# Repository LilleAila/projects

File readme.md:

# Small programming projects

Some small projects organized by year and month with development environments managed by nix and direnv

## Devshell templates
Usage:
```bash
# .envrc
use flake github:LilleAila/projects#nix
use flake github:LilleAila/projects#python
use nix
```
```nix
# shell.nix
{ pkgs ? import <nixpkgs> {} }: with pkgs; mkShell {
  nativeBuildInputs = [
    (python311.withPackages (ps: with ps; [
      matplotlib
      numpy
      tkinter
    ]))
  ];
}
```

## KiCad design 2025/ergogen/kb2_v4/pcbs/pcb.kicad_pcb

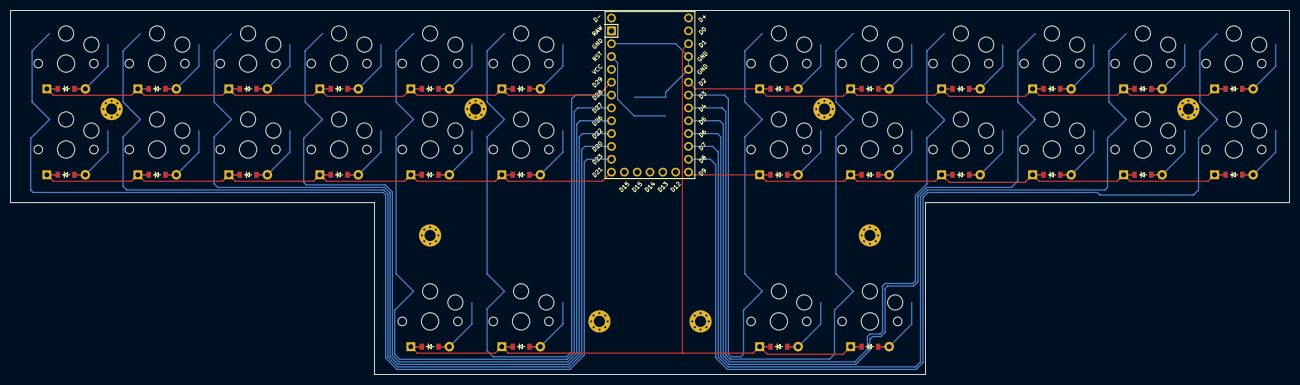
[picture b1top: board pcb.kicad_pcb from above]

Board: 2 copper layers, 253.0 x 72.0 mm, 66 parts (0 on the bottom side), 47 nets.

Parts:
B1: SW_TACT_ALPS_SKQGABE010
D1, D2, D3, D4, D5, D6, D7, D8, D9, D10, D11, D12, D13, D14, D15, D16, D17, D18, D19, D20, D21, D22, D23, D24, D25, D26, D27, D28: ComboDiode
MCU1: ProMicro
S1, S2, S3, S4, S5, S6, S7, S8, S9, S10, S11, S12, S13, S14, S15, S16, S17, S18, S19, S20, S21, S22, S23, S24, S25, S26, S27, S28: PG1350
_1, _2, _3, _4, _5, _6, _7, _8: Mount_Hole_2.2mm_Pad_Via

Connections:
D1: D25.1, D26.1, D27.1, D28.1, MCU1.20
D2: D14.1, D16.1, D18.1, D20.1, D22.1, D24.1, MCU1.23
D3: MCU1.24, S13.1, S14.1, S27.1
D4: MCU1.25, S15.1, S16.1, S28.1
D5: MCU1.26, S17.1, S18.1
D6: MCU1.27, S19.1, S20.1
D7: MCU1.28, S21.1, S22.1
D8: MCU1.29, S23.1, S24.1
D9: D13.1, D15.1, D17.1, D19.1, D21.1, D23.1, MCU1.30
D20: MCU1.10, S3.1, S4.1
D21: D1.1, D3.1, D5.1, D7.1, D9.1, D11.1, MCU1.12
D22: MCU1.9, S5.1, S6.1
D23: MCU1.11, S1.1, S2.1
D26: MCU1.8, S7.1, S8.1
D27: MCU1.7, S9.1, S10.1, S25.1
D28: MCU1.6, S11.1, S12.1, S26.1
D29: D2.1, D4.1, D6.1, D8.1, D10.1, D12.1, MCU1.5
GND: B1.1, MCU1.2, MCU1.21, MCU1.22
RST: B1.2, MCU1.3
index_lbottom: D9.2, S9.2
index_ltop: D10.2, S10.2
index_rbottom: D15.2, S15.2
index_rtop: D16.2, S16.2
inner_lbottom: D11.2, S11.2
inner_ltop: D12.2, S12.2
inner_lttop: D26.2, S26.2
inner_rbottom: D13.2, S13.2
inner_rtop: D14.2, S14.2
inner_rttop: D27.2, S27.2
middle_lbottom: D7.2, S7.2
middle_ltop: D8.2, S8.2
middle_rbottom: D17.2, S17.2
middle_rtop: D18.2, S18.2
outer_lbottom: D1.2, S1.2
outer_ltop: D2.2, S2.2
outer_lttop: D25.2, S25.2
outer_rbottom: D23.2, S23.2
outer_rtop: D24.2, S24.2
outer_rttop: D28.2, S28.2
pinky_lbottom: D3.2, S3.2
pinky_ltop: D4.2, S4.2
pinky_rbottom: D21.2, S21.2
pinky_rtop: D22.2, S22.2
ring_lbottom: D5.2, S5.2
ring_ltop: D6.2, S6.2
ring_rbottom: D19.2, S19.2
ring_rtop: D20.2, S20.2

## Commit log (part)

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2024-07-08 Initial commit
    Added devshells and stuff
2024-07-08 added python
2024-07-08 added js
2024-07-08 added missing stuff to js shell
2024-07-08 added astro shel
2024-07-08 added texlive
2024-07-08 fixed pyright in python shell
2024-07-08 added stuff to readme
2024-07-08 added lua
2024-07-08 added rust
2024-07-08 added rust anal
2024-07-10 ting og sånt
2024-08-19 did some stuff
2024-08-21 jupyter: init
2024-08-22 el eller annen oppgave
2024-08-26 kapittel 1a
2024-08-26 TYPES
2024-08-26 updated til python 3.12
2024-08-29 stein saks papir
2024-08-29 bedre kode og masse kommentarer
2024-08-29 stop unnecessary __init__ when stopping
2024-08-29 mulige forbedringer
2024-08-29 reversed the choices list to be correct when inputting
2024-09-04 tried adding manim
2024-09-05 manim stuff
2024-09-05 readme
2024-09-05 bruker-innlogging med hashing og sånt
2024-09-05 mer ting
2024-09-07 bedre struktur på 03
2024-09-07 skrive oppgaven i 03
2024-09-07 ignore __pycache__
2024-09-07 ignore db in 03
2024-09-07 path arg for db
2024-09-12 masse greie
2024-09-12 quicksort
2024-09-12 tested different activity diagrams
2024-09-13 fikse duplikat
2024-09-14 web scraping stuff
2024-09-15 tried doing unibok dl
2024-09-15 better uml diagram
2024-09-15 unibok ting
2024-09-15 mer unibok ting
2024-09-15 unibok: download file
2024-09-15 get chromium path automatically
2024-09-15 class and better code for unibok thing
2024-09-15 ability to download multiple books
2024-09-15 download entire library
2024-09-16 grenseverdier
2024-09-16 dicts
2024-09-17 ; instead of ,
2024-09-19 fucnitojasner
2024-09-20 project euler problems
2024-09-20 fix type in problem 6
2024-09-20 project euler problem 8
2024-09-20 project euler problem 10
2024-09-20 organize stuff
2024-09-20 project euler readme
2024-09-20 problem 12
2024-09-20 problem 14
2024-09-21 problem 13
2024-09-21 problem 15
2024-09-21 problem 16
2024-09-23 prøve 20240923
2024-09-25 problem 11
2024-09-25 problem 20
2024-09-26 oppdatert koden litt
2024-09-27 unibok: fix path names with /
2024-10-05 proecteuler: renamed files
2024-10-05 p017
2024-10-06 akademika author to calibre format
2024-10-24 diagram for spill
2024-10-24 finish diagram for game
2024-10-28 enemy interface in 10-
2024-10-29 ting
2024-10-31 sudoku ting
2024-10-31 more sudoku
2024-11-01 more progress on sudoku solver
    missing validation function
2024-11-04 finished solver but extremely inefficient
2024-11-05 significantly improve speed
2024-11-06 completely choose pos automatically rather than increment by one in parent
2024-11-06 started doing random stuff in board generation
2024-11-11 pygame: init
2024-11-11 pygame better organization
2024-11-11 oida lol
2024-11-14 more ponging
2024-11-14 paddle collision
2024-11-14 show score
2024-11-14 better score class
2024-11-14 point x value
2024-11-15 animations
2024-11-15 runtime didn't work on graph :(
2024-11-15 more manim stuff
2024-11-16 kontinuitet
2024-11-16 mobject for point on graph
2024-11-16 mer kontinuitet
2024-11-17 organized stuff better
2024-11-17 move both animations into one file
2024-11-18 secant approaching each side
2024-11-18 --amend
2024-11-18 tweak stuff
2024-11-18 derivative to a
2024-11-18 mer derivasjon
2024-11-21 some collision stuff
2024-11-21 fix ball clipping
2024-11-25 Add 1 git-crypt collaborator
    New collaborators:
    2B9B9799 Olai Solsvik <olai.solsvik@gmail.com>
2024-11-25 manim: play audio, git-crypt: init and encrypt manim audio
2024-11-25 start doing bibliotek
2024-11-25 start tui
2024-11-25 more book stuff
2024-11-25 puml diagram
2024-11-25 small tweaks in manim
2024-11-26 heldagsprøve 2024-11-26
2024-11-26 mer heldagsprøve ting
2024-11-27 started adding audio in manim
2024-11-27 remove ceil left from debugging
2024-11-28 manim: add sounds
2024-12-01 julekalendere: init
2024-12-01 knowit: luke 1
2024-12-01 adventofcode: day 1
2024-12-02 knowit: luke 2
2024-12-02 aoc: day 2
2024-12-02 knowit: remove compile stuff
2024-12-03 knowit: start luke 2
2024-12-03 more luke 3
2024-12-03 more knowit 3 aaa
2024-12-03 aoc: day 3
2024-12-03 day 3 aoc explain dotall
2024-12-03 aaaaa
2024-12-04 knowit luke 4
2024-12-05 aoc 4 pt1
2024-12-06 knowit luke 6 start
2024-12-07 luke 6 (ikke ferdig :()
2024-12-07 knowit: luke 7
2024-12-07 knowit: challenges note in readme
2024-12-07 remove unused import
2024-12-08 tried fixing day 6 knowit
2024-12-08 knowit: luke 8
2024-12-08 luke 8 knowit: small time improvement
2024-12-08 gitignore haskell build artefacts
2024-12-08 luke 4 readme and notes
2024-12-09 continued with 6
2024-12-09 remove compiled
2024-12-09 knowit: luke 9
2024-12-09 luke 3 knowit: tried python 😭
2024-12-09 luke 9: tweak syntax
2024-12-10 luke 1: fix small error
2024-12-11 tried doing luke 10
2024-12-11 fixed stupid error i don't even know where came from
2024-12-11 started solving luke 11
2024-12-11 cpp stuff
2024-12-11 finish day 6
2024-12-12 started solving 12
2024-12-12 tried doing more luke 11 :(
2024-12-12 a* search
2024-12-12 get the distance
2024-12-12 more stuff
2024-12-12 tried python on 12
2024-12-12 init potensiell prøve
2024-12-14 tried doing 14
2024-12-15 map ting
2024-12-15 14 readme
2024-12-15 tried starting 15
2024-12-15 tried more on 13
2024-12-24 luke 24
2025-01-06 knowit: add challenges
2025-01-13 nio runde 2
2025-01-16 it2: 14-datasett
2025-01-20 start openstreetmap thing
2025-01-20 simplify api call
2025-01-20 cut off outside bounding box
2025-01-20 get coords from user input
2025-01-21 generate simple 3d model
2025-01-21 clean up
2025-01-21 get epsg automatically
2025-01-21 base plate and walls
2025-01-21 simplify plotting
2025-01-21 area selection and notes
2025-01-21 fix dependencies
2025-01-21 increate base plate height
2025-01-23 it2 oppgaver
2025-01-27 start trying to add jupyter lab
2025-01-27 oppgaver it2
2025-01-30 plotting lol
2025-02-01 started looking at monkeytype stats
2025-02-03 matplotlib
2025-02-06 tried more jupyterlab
2025-02-06 pandas greier
2025-02-06 fikse tall i navn
2025-02-06 add monkeytype and cstimer stuff
2025-02-06 add studietid datasets
2025-02-06 cstimer plotting lol
2025-02-06 studietid
2025-02-06 started monkeytyping
2025-02-06 mer studietid og monkeytype
2025-02-08 add anki and koreader datasets
2025-02-08 book stats
2025-02-08 more koreader
2025-02-09 more koreader 2
2025-02-09 make lsp not error when not error
2025-02-09 anki stats
2025-02-09 anki stat labels
2025-02-09 anki review efficiency
2025-02-09 small diagram tweaks
2025-02-09 more book statistics
2025-02-09 tried more to get jupyterlab to work :(
2025-02-09 jupyterlab: yay it vørk
2025-02-10 github commit greier
2025-02-10 jupyter greier
2025-02-11 studietid, native anki
2025-02-11 fikse studietid csv
2025-02-11 ferdig med å un-pandase
2025-02-11 fix units in native impl
2025-02-11 anki: remove unused dependency
2025-02-11 anki: add file description to readme
2025-02-16 noen greier
2025-02-17 osm: general improvements
2025-02-17 osm: more oop, colors
2025-02-18 osm: pick location by address
2025-02-18 osm: better oop
2025-02-18 osm: small tweaks
2025-02-20 koreader: init
2025-02-20 datasett: test efficiency
2025-02-20 datasett: continue comparing pandas / native
2025-02-23 osm: gui
2025-02-23 osm: gui with correct colors
2025-03-06 Bilde greir
2025-03-06 gøyere bilder
2025-03-09 ergogen
2025-03-09 git ignore .DS_Store
2025-03-09 ergogen init stuff
2025-03-09 better row and column nets
2025-03-09 more ergogen
2025-03-09 change pins for keys
2025-03-09 finish wiring
2025-03-09 small pcb tweaks, generate gerber
2025-03-09 slice case
2025-03-10 it2: add sympy
2025-03-10 ergogen: add bom to keyboard
2025-03-10 ergogen ting
2025-03-10 init tvers
2025-03-10 drag stuff
2025-03-10 frood controller stuff
2025-03-10 route pcb
2025-03-11 complete bom
2025-03-13 more ergogen stuff again
2025-03-13 eregegoegaoegne
2025-03-13 more progress on keyboard
2025-03-14 promicro cutout on top case
2025-03-14 spacing between pcb and case
2025-03-14 more progress on kb3v3
2025-03-14 route pcb, plot gerbers
2025-03-17 ergogen: add new with more columns
2025-03-17 ergogen: add new column to v4 of keybaord
2025-03-20 ergogeng finish? case.
2025-03-20 it2 prøve 2025-03-20
2025-03-21 tweak screw size
2025-03-24 regresjon greir
2025-03-27 2025-03-27T09:43+01:00
2025-03-31 testing
2025-04-02 2025-04-02T08:17+02:00
2025-04-03 2025-04-03T10:39+02:00
2025-04-03 2025-04-03T16:14+02:00
2025-04-03 2025-04-03T20:12+02:00
2025-04-15 ergogen in nix
2025-04-17 ergogen: re write config in js
2025-04-17 finish? keyboard
2025-04-18 move screw holes to not interfere with switches
2025-04-19 a bunch more keyboard stuff
2025-04-22 more better bom
2025-04-27 r1 ting
2025-04-27 it2: add pygame
2025-04-28 oop, test oop
2025-04-28 mer prøve greier
2025-04-29 prøve greier
2025-05-01 do stuff
2025-05-12 it2: pip
2025-06-13 ergogen stuff
2025-06-17 ti. 17. juni 19:30:19 +0200 2025
2025-09-12 it1: 02-html-basics
2025-09-16 it1: 03-flex-and-stuff
2025-09-18 r2: fourier stuff
2025-09-19 it1: 04-more-css
2025-09-23 it1: sjakk
2025-09-26 extract it1
2025-09-29 move skole into subfolder, fysikk 366
2025-09-30 r2 ting
2025-10-15 fysikk ting
2025-10-24 euler: 025
2025-10-24 euler: 022
2025-10-24 euler: 27 and wip 23
2025-10-24 euler: 024
2025-11-11 integral
2025-12-01 knowit: 01
2025-12-01 reverse lists
2025-12-01 hs with data
2025-12-01 better head'
2025-12-02 knowit 02
2025-12-03 knowit 03
2025-12-03 small tweaks
2025-12-04 manim
2025-12-04 knowit 04
2025-12-05 knowit 05
2025-12-05 aoc stuff
2025-12-06 knowit 6
2025-12-06 flatten year
2025-12-07 knowit 07
2025-12-07 remove tails stuff
2025-12-07 remove unused code
2025-12-08 knowit 08
2025-12-09 knowit 09
2025-12-09 knowit 09 putStr
2025-12-09 knowit 09 bean type
2025-12-10 r1 prøve, knowit 10
2025-12-11 knowit 11
2025-12-11 tof dataanalyse
2025-12-12 knowit 12
2025-12-13 knowit 13
2025-12-14 knowit 14
2025-12-15 knowit 15
2025-12-16 knowit 16
2025-12-17 not knowit 17 😔
2025-12-17 try interpreting roll differently
2025-12-17 Revert "try interpreting roll differently"
    This reverts commit 4d2abb43003f13d3d27c3bd7bce398aec0d7c717.
2025-12-17 remove commented lines
2025-12-19 knwoit 18
2025-12-20 knowit attempt to do 19
2025-12-20 knowit 20
2025-12-21 knwoit 21
2025-12-22 knowit 22
2025-12-23 knowit 23
2025-12-24 not knowit 24
2025-12-25 aaaaaaaaaaaaaaaaaaaaaaaaaa
2026-01-12 people
2026-01-19 add dependencies or something
2026-01-20 tof grafer
2026-01-22 tof prøve 2026-01-22
2026-01-26 tof: 3d modeling
2026-01-29 skole/tof1: cading
2026-01-29 gitignore: add *.FCBak
2026-01-31 tof: more 3d modeling
2026-02-02 tof: more modeling
2026-02-05 tof: arduino box
2026-02-05 tof: arduino box lid
2026-02-22 bt page turner
2026-02-24 schrödinger stuff
2026-02-25 attempt to render hydrogen with spherical grid
    this worked although converting from cartesian to spherical created
    better results than starting with a spherical coordinate system
2026-02-27 atom change resolution 40 -> 50
2026-03-06 bt page turner wip
2026-03-08 page turner: try hijelhid
2026-03-23 ordstorm greie
2026-04-30 starte på programmeringsoppgave i fysikk
2026-04-30 test with alpha particle
2026-04-30 mer arbeid på programmeringsinnleveringen
2026-04-30 alfapartikkel
2026-05-01 work on 2d
2026-05-01 tweak code
2026-05-02 ferdig med fysikk innlevering
2026-05-02 cleanup
2026-05-06 skole greier idk
2026-05-12 steg lsb encoding
2026-05-20 tof greier or sång
2026-05-21 mye rart
2026-05-27 more tof presentation
2026-05-27 reduce toc font size
2026-06-08 eksamen greier
2026-06-10 mer eksamen greier
2026-06-10 abcdefghijklmnop
